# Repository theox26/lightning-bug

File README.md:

# lightning-bug
Eagle files for Little Bits Custom part

Sadly, I lost the arduino code and the other files for this project. The board file was still saved at OSH Park where I had the PCB made.

I am rebuilding the schematic file from the board file and the finished prototype.

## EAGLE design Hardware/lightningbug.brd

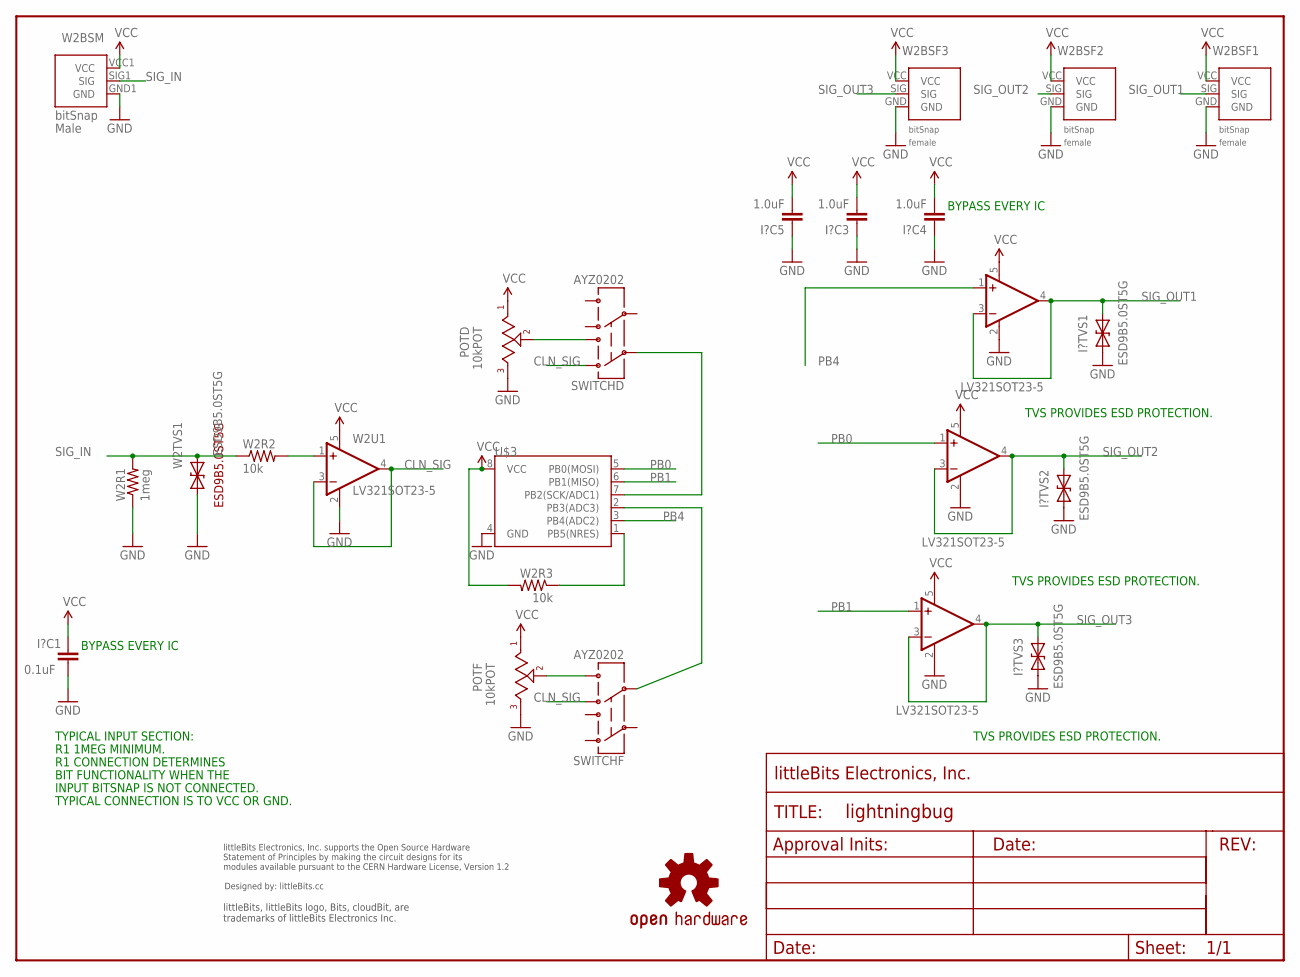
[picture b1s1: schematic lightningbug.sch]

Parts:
FRAME1: FRAME-LETTER; FABDWG01-OHW
I?C1: 0.1uF; CAP-0603
I?C3, I?C4, I?C5: 1.0uF; CAP-0603
I?TVS1, I?TVS2, I?TVS3: ESD9B5.0ST5G; SOD-923
POTD: 10kPOT; TRIMPOT_SMD_3MM
POTF: 10kPOT; TRIMPOT_SMD_3MM
SWITCHD: AYZ0202
SWITCHF: AYZ0202
U1, U2, U3: LV321SOT23-5; SOT23-5
U$1: OSHWCREDIT
U$3: ATTINY85; SO08-EIAJ
U$6: OSHW-LOGOL; OSHW-LOGO-L
W2BSF1, W2BSF2, W2BSF3: BITSNAP_V03_FEMALE
W2BSM: BITSNAP_V03_MALE
W2R1: 1meg; RES-0603
W2R2, W2R3: 10k; RES-0603
W2TVS1: ESD9B5.0ST5G; SOD-923
W2U1: LV321SOT23-5; SOT23-5

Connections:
CLN_SIG: SWITCHD.1, SWITCHF.4, W2U1.3 (-IN), W2U1.4 (OUT)
GND: I?C1.2, I?C3.1, I?C4.1, I?C5.1, I?TVS1.1 (A), I?TVS2.1 (A), I?TVS3.1 (A), POTD.3, POTF.3, U1.2 (V-), U2.2 (V-), U3.2 (V-), U$3.4 (GND), W2BSF1.GND, W2BSF2.GND, W2BSF3.GND, W2BSM.GND1 (GND), W2R1.1, W2TVS1.1 (A), W2U1.2 (V-)
unnamed: POTF.2, SWITCHF.6
unnamed: W2R2.2, W2U1.1 (+IN)
unnamed: POTD.2, SWITCHD.3
NRES: U$3.1 (PB5(NRES)), W2R3.1
PB0: U2.1 (+IN), U$3.5 (PB0(MOSI))
PB1: U3.1 (+IN), U$3.6 (PB1(MISO))
PB2: SWITCHD.2, U$3.7 (PB2(SCK/ADC1))
PB3: SWITCHF.5, U$3.2 (PB3(ADC3))
PB4: U1.1 (+IN), U$3.3 (PB4(ADC2))
SIG_IN: W2BSM.SIG1 (SIG), W2R1.2, W2R2.1, W2TVS1.2 (C)
SIG_OUT1: I?TVS1.2 (C), U1.3 (-IN), U1.4 (OUT), W2BSF1.SIG
SIG_OUT2: I?TVS2.2 (C), U2.3 (-IN), U2.4 (OUT), W2BSF2.SIG
SIG_OUT3: I?TVS3.2 (C), U3.3 (-IN), U3.4 (OUT), W2BSF3.SIG
VCC: I?C1.1, I?C3.2, I?C4.2, I?C5.2, POTD.1, POTF.1, U1.5 (V+), U2.5 (V+), U3.5 (V+), U$3.8 (VCC), W2BSF1.VCC, W2BSF2.VCC, W2BSF3.VCC, W2BSM.VCC1 (VCC), W2R3.2, W2U1.5 (V+)

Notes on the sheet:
R1 1MEG MINIMUM.
R1 CONNECTION DETERMINES
BIT FUNCTIONALITY WHEN THE
INPUT BITSNAP IS NOT CONNECTED.
TYPICAL CONNECTION IS TO VCC OR GND.
TYPICAL INPUT SECTION:
TVS PROVIDES ESD PROTECTION.
BYPASS EVERY IC

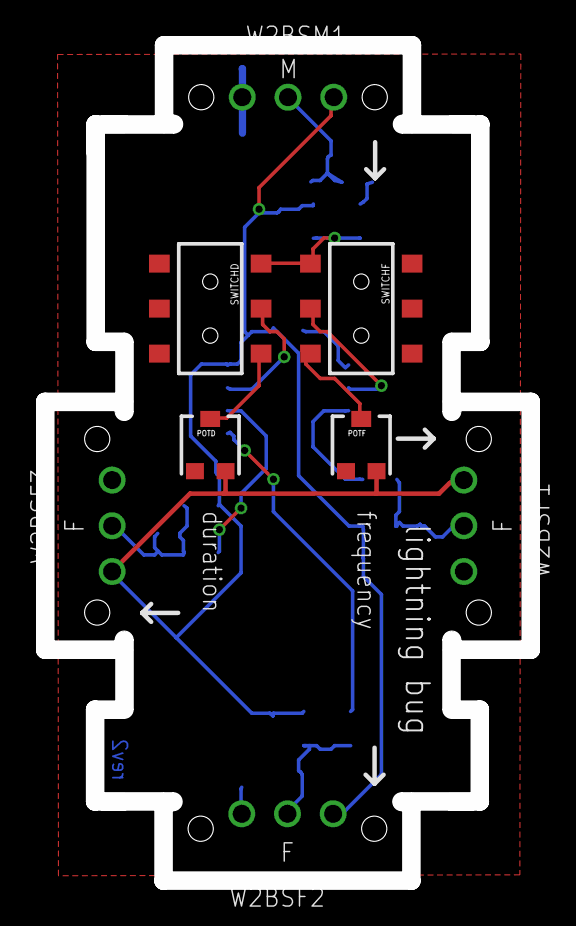
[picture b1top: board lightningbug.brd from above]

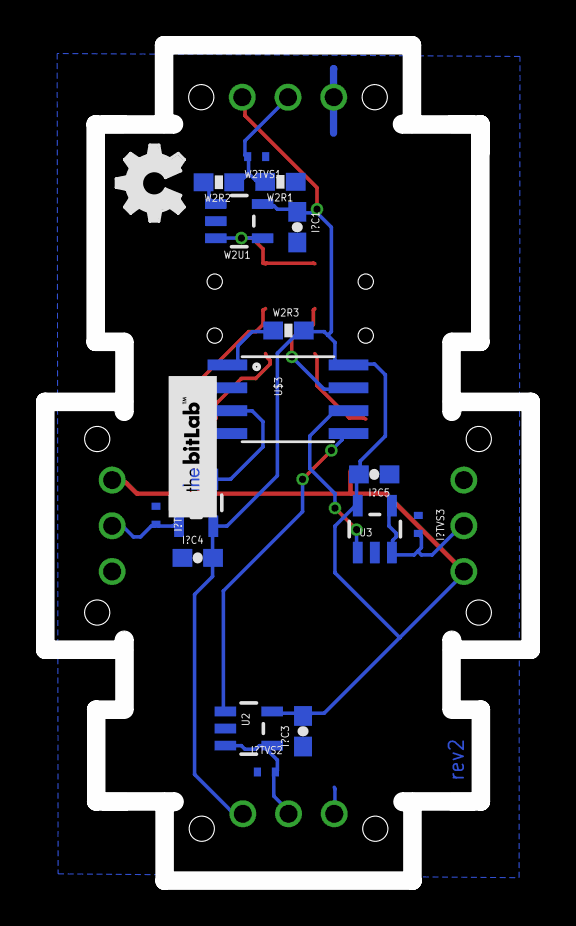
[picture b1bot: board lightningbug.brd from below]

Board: 2 copper layers, 27.0 x 46.4 mm, 29 parts (16 on the bottom side), 16 nets.

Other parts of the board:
U$2: BITLAB-LOGO
U$5: OSHW_FILLX150_NOTEXT

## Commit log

2017-12-05 board file
2017-12-05 brd file
2017-12-05 description
2017-12-05 updating sch from base LB version
2017-12-06 schematic in process
2017-12-08 connected sch and brd
2017-12-09 moved Eagle files
2017-12-09 base firmware from LilyTwinkle

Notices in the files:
parts and their libraries:
LITTLEBITS: modules available pursuant to the CERN Hardware License,
Version 1.2
LITTLEBITS: modules available pursuant to the CERN Hardware License, Version 1.2
